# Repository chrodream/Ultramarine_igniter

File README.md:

# Ultramarine Igniter

## Specification

- Ergonomic key style
- OLED unit
- QMK Firmware is Ready
- RGB LED matrix (Optional)
- Li-Po Battery charge circuit included (Optional)

## Parts

- Ultramarine PCBs x 2
- Key switches x 70 (Cherry MX and Kailh low profile v1 are available)
- 1N4148W Diode x 70
- Pro micro x 70 (You can use BLE Pro micro when connect with Bluetooth)
- Reset switches x 2
- TRRS cable x 1 (Only wired connection)

### Optional parts

- SK6812 mini x 70

- OLED working with SSD1306 driver x 2 (128 x 32 pixels)

  #### Battery parts

  - Li-Po batteries x 2 
  - pCh MOSFET (Recommended AO3401)
  - MCP73831
  - DW01A
  - FS8205
  - 4.7uF Capacitor x 3
  - 0.1uF x 1
  - 0.1 Resistor x 1
  - 330

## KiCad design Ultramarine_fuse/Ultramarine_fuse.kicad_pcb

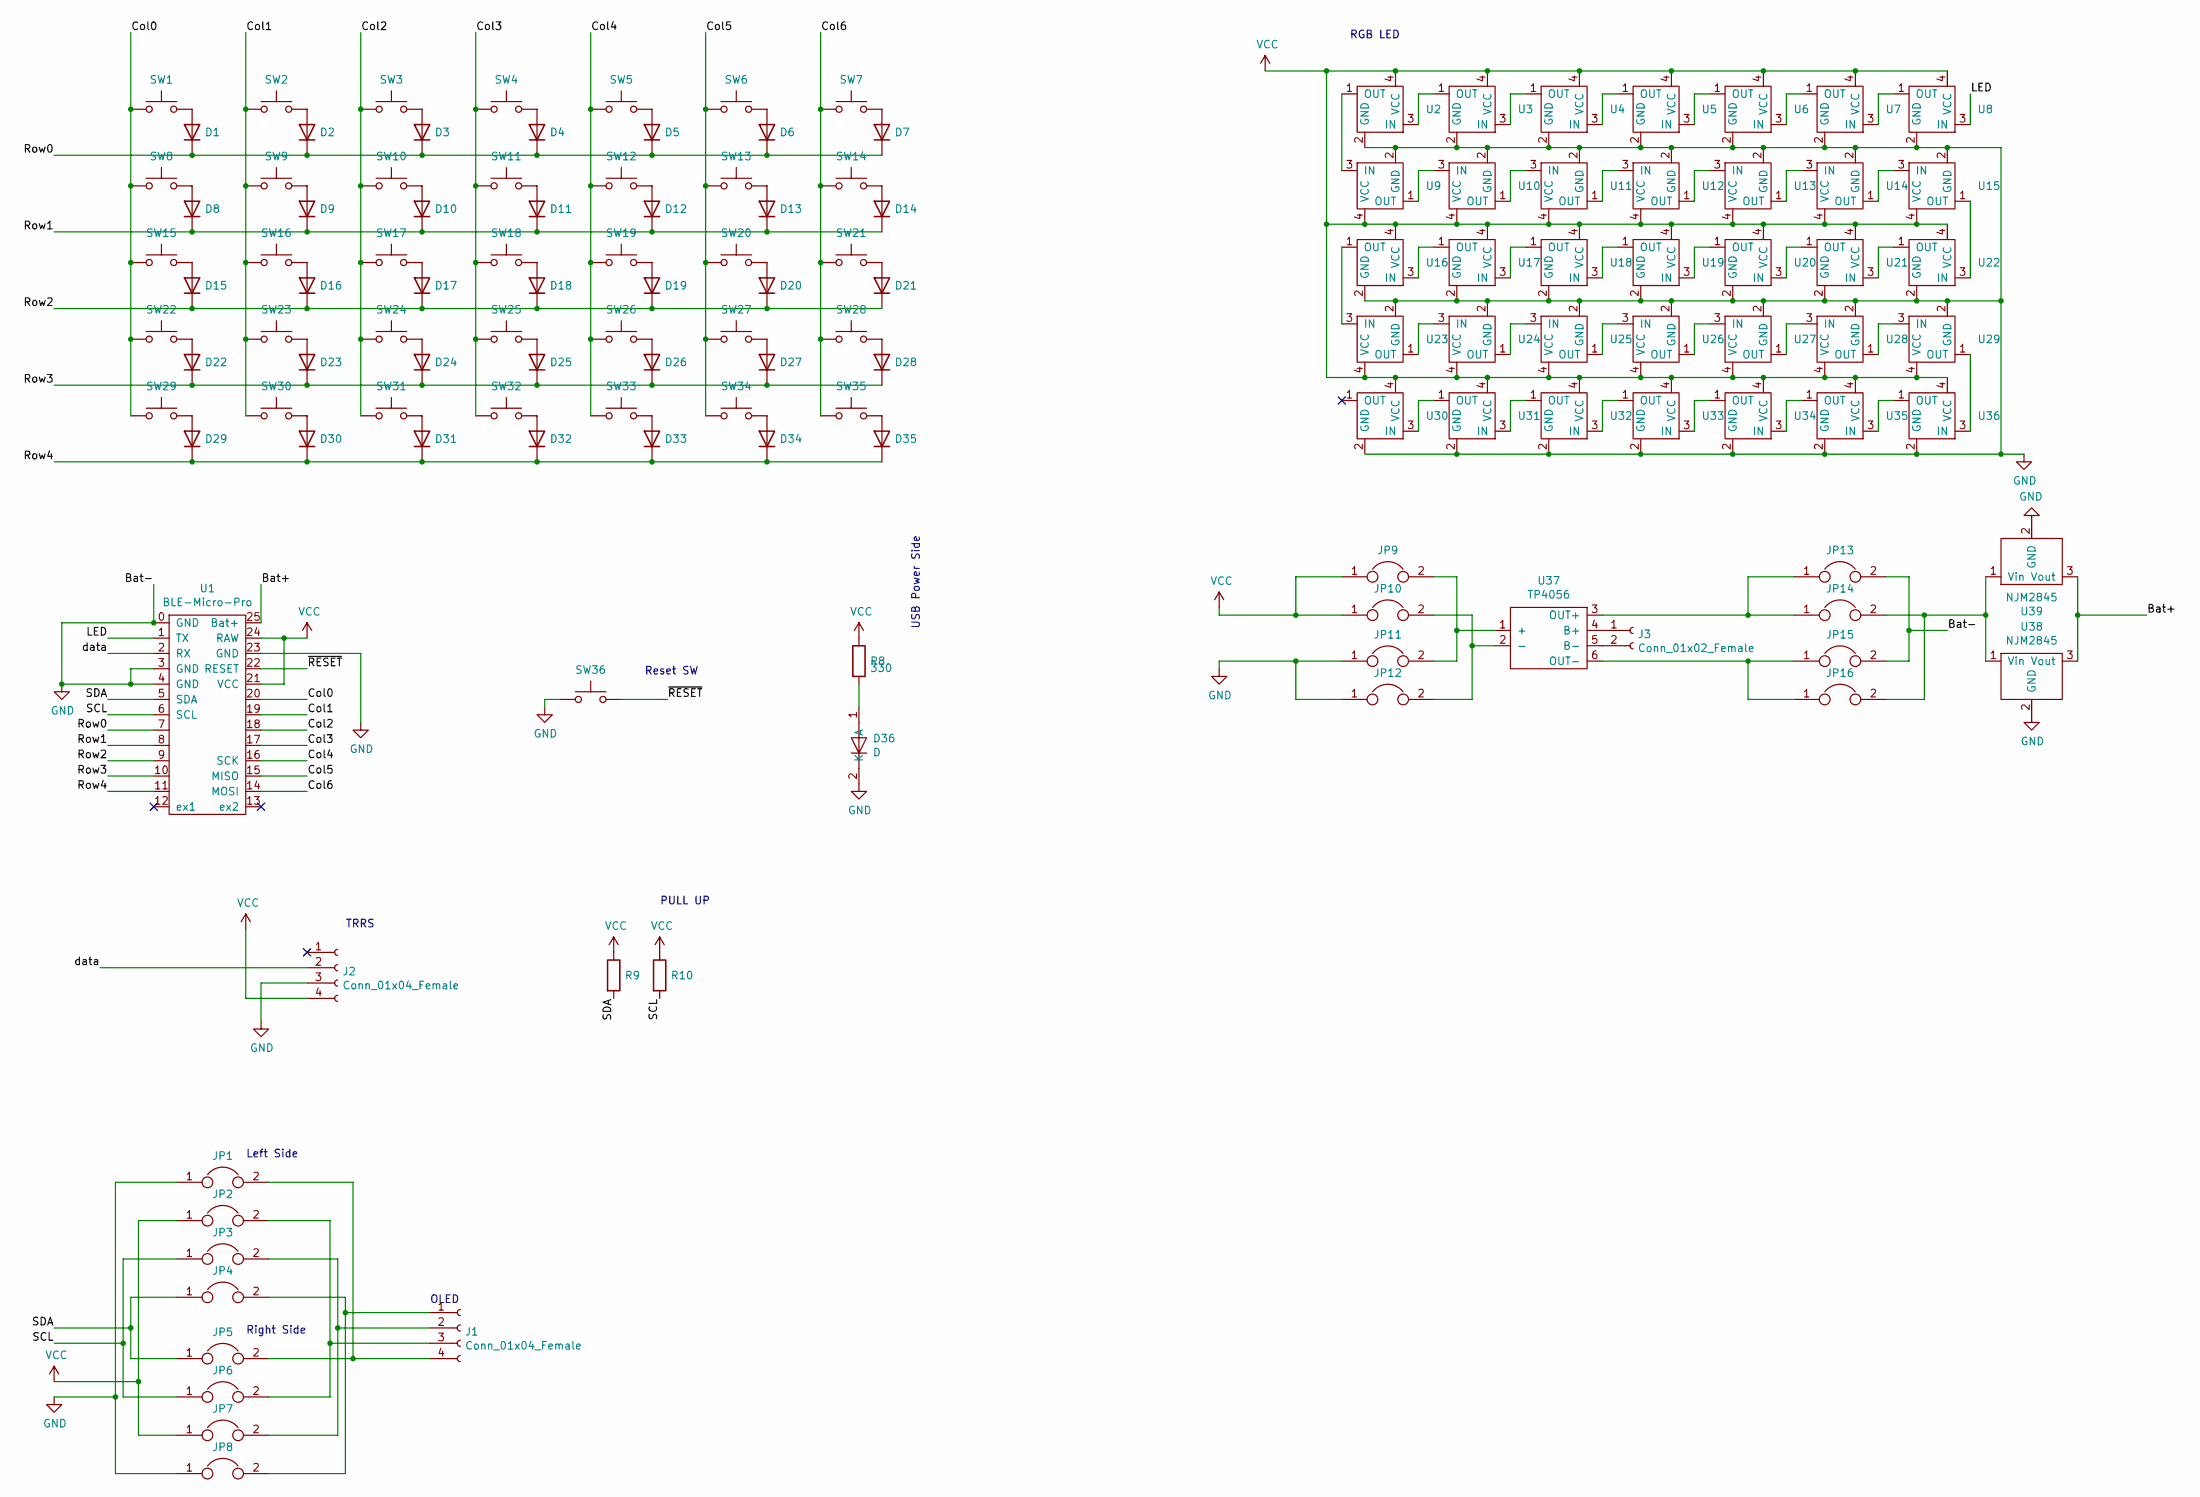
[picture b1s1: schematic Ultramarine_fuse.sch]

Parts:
D1, D2, D3, D4, D5, D6, D7, D8, D9, D10, D11, D12, D13, D14, D15, D16, D17, D18, D19, D20, D21, D22, D23, D24, D25, D26, D27, D28, D29, D30, D31, D32, D33, D34, D35: D; 1N4148
D36: D; LED1608
J1: Conn_01x04_Female; 4pin_A
J2: Conn_01x04_Female; TRRS
J3: Conn_01x02_Female; S2B-PH-K-S
JP1, JP2, JP3, JP4, JP5, JP6, JP7, JP8: Jumper; SMD_Jumper
JP9, JP10, JP11, JP12, JP13, JP14, JP15, JP16: Jumper; SolderJumper-2_P1.3mm_Open_RoundedPad1.0x1.5mm
R8: 330; 1608
R9, R10: 10K; 1608
SW1, SW2, SW3, SW4, SW5, SW6, SW7, SW8, SW9, SW10, SW11, SW12, SW13, SW14, SW15, SW16, SW17, SW18, SW19, SW20, SW21, SW22, SW23, SW24, SW25, SW26, SW27, SW28, SW29, SW30, SW31, SW32, SW33, SW34, SW35: SW_Push; MX-Kailh
SW36: SW_Push; TactSW
U1: BLE-Micro-Pro
U2, U3, U4, U5, U6, U7, U8, U9, U10, U11, U12, U13, U14, U15, U16, U17, U18, U19, U20, U21, U22, U23, U24, U25, U26, U27, U28, U29, U30, U31, U32, U33, U34, U35, U36: SK6812mini
U37: TP4056
U38, U39: NJM2845; TO-252-2

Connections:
/Bat+: U1.25 (Bat+), U38.3 (Vout), U39.3 (Vout)
/Col0: SW1.1, SW8.1, SW15.1, SW22.1, SW29.1, U1.20
/Col1: SW2.1, SW9.1, SW16.1, SW23.1, SW30.1, U1.19
/Col2: SW3.1, SW10.1, SW17.1, SW24.1, SW31.1, U1.18
/Col3: SW4.1, SW11.1, SW18.1, SW25.1, SW32.1, U1.17
/Col4: SW5.1, SW12.1, SW19.1, SW26.1, SW33.1, U1.16 (SCK)
/Col5: SW6.1, SW13.1, SW20.1, SW27.1, SW34.1, U1.15 (MISO)
/Col6: SW7.1, SW14.1, SW21.1, SW28.1, SW35.1, U1.14 (MOSI)
/LED: U1.1 (TX), U8.3 (IN)
/Row0: D1.1 (K), D2.1 (K), D3.1 (K), D4.1 (K), D5.1 (K), D6.1 (K), D7.1 (K), U1.7
/Row1: D8.1 (K), D9.1 (K), D10.1 (K), D11.1 (K), D12.1 (K), D13.1 (K), D14.1 (K), U1.8
/Row2: D15.1 (K), D16.1 (K), D17.1 (K), D18.1 (K), D19.1 (K), D20.1 (K), D21.1 (K), U1.9
/Row3: D22.1 (K), D23.1 (K), D24.1 (K), D25.1 (K), D26.1 (K), D27.1 (K), D28.1 (K), U1.10
/Row4: D29.1 (K), D30.1 (K), D31.1 (K), D32.1 (K), D33.1 (K), D34.1 (K), D35.1 (K), U1.11
/SCL: JP3.1, JP6.1, R10.2, U1.6 (SCL)
/SDA: JP4.1, JP5.1, R9.2, U1.5 (SDA)
/data: J2.2, U1.2 (RX)
/~RESET: SW36.2, U1.22 (RESET)
GND: D36.2 (K), J2.3, JP1.1, JP8.1, JP11.1, JP12.1, JP13.2, JP15.2, SW36.1, U1.0 (GND), U1.3 (GND), U1.4 (GND), U1.23 (GND), U2.2 (GND), U3.2 (GND), U4.2 (GND), U5.2 (GND), U6.2 (GND), U7.2 (GND), U8.2 (GND), U9.2 (GND), U10.2 (GND), U11.2 (GND), U12.2 (GND), U13.2 (GND), U14.2 (GND), U15.2 (GND), U16.2 (GND), U17.2 (GND), U18.2 (GND), U19.2 (GND), U20.2 (GND), U21.2 (GND), U22.2 (GND), U23.2 (GND), U24.2 (GND), U25.2 (GND), U26.2 (GND), U27.2 (GND), U28.2 (GND), U29.2 (GND), U30.2 (GND), U31.2 (GND), U32.2 (GND), U33.2 (GND), U34.2 (GND), U35.2 (GND), U36.2 (GND), U38.2 (GND), U39.2 (GND)
unnamed: D1.2 (A), SW1.2
unnamed: D2.2 (A), SW2.2
unnamed: D3.2 (A), SW3.2
unnamed: D4.2 (A), SW4.2
unnamed: D5.2 (A), SW5.2
unnamed: D6.2 (A), SW6.2
unnamed: D7.2 (A), SW7.2
unnamed: D8.2 (A), SW8.2
unnamed: D9.2 (A), SW9.2
unnamed: D10.2 (A), SW10.2
unnamed: D11.2 (A), SW11.2
unnamed: D12.2 (A), SW12.2
unnamed: D13.2 (A), SW13.2
unnamed: D14.2 (A), SW14.2
unnamed: D15.2 (A), SW15.2
unnamed: D16.2 (A), SW16.2
unnamed: D17.2 (A), SW17.2
unnamed: D18.2 (A), SW18.2
unnamed: D19.2 (A), SW19.2
unnamed: D20.2 (A), SW20.2
unnamed: D21.2 (A), SW21.2
unnamed: D22.2 (A), SW22.2
unnamed: D23.2 (A), SW23.2
unnamed: D24.2 (A), SW24.2
unnamed: D25.2 (A), SW25.2
unnamed: D26.2 (A), SW26.2
unnamed: D27.2 (A), SW27.2
unnamed: D28.2 (A), SW28.2
unnamed: D29.2 (A), SW29.2
unnamed: D30.2 (A), SW30.2
unnamed: D31.2 (A), SW31.2
unnamed: D32.2 (A), SW32.2
unnamed: D33.2 (A), SW33.2
unnamed: D34.2 (A), SW34.2
unnamed: D35.2 (A), SW35.2
unnamed: D36.1 (A), R8.2
unnamed: J1.1, JP4.2, JP8.2
unnamed: J1.2, JP3.2, JP7.2
unnamed: J1.3, JP2.2, JP6.2
unnamed: J1.4, JP1.2, JP5.2
unnamed: J3.1, U37.4 (B+)
unnamed: J3.2, U37.5 (B-)
unnamed: JP10.2, JP12.2, U37.2 (-)
unnamed: JP9.2, JP11.2, U37.1 (+)
unnamed: JP13.1, JP14.1, U37.3 (OUT+)
unnamed: JP14.2, JP16.2, U38.1 (Vin), U39.1 (Vin)
unnamed: JP15.1, JP16.1, U37.6 (OUT-)
unnamed: U2.1 (OUT), U9.3 (IN)
unnamed: U2.3 (IN), U3.1 (OUT)
unnamed: U3.3 (IN), U4.1 (OUT)
unnamed: U4.3 (IN), U5.1 (OUT)
unnamed: U5.3 (IN), U6.1 (OUT)
unnamed: U6.3 (IN), U7.1 (OUT)
unnamed: U7.3 (IN), U8.1 (OUT)
unnamed: U10.1 (OUT), U11.3 (IN)
unnamed: U9.1 (OUT), U10.3 (IN)
unnamed: U11.1 (OUT), U12.3 (IN)
unnamed: U12.1 (OUT), U13.3 (IN)
unnamed: U13.1 (OUT), U14.3 (IN)
unnamed: U14.1 (OUT), U15.3 (IN)
unnamed: U15.1 (OUT), U22.3 (IN)
unnamed: U16.1 (OUT), U23.3 (IN)
unnamed: U16.3 (IN), U17.1 (OUT)
unnamed: U17.3 (IN), U18.1 (OUT)
unnamed: U18.3 (IN), U19.1 (OUT)
unnamed: U19.3 (IN), U20.1 (OUT)
unnamed: U20.3 (IN), U21.1 (OUT)
unnamed: U21.3 (IN), U22.1 (OUT)
unnamed: U23.1 (OUT), U24.3 (IN)
unnamed: U24.1 (OUT), U25.3 (IN)
unnamed: U25.1 (OUT), U26.3 (IN)
unnamed: U26.1 (OUT), U27.3 (IN)
unnamed: U27.1 (OUT), U28.3 (IN)
unnamed: U28.1 (OUT), U29.3 (IN)
unnamed: U29.1 (OUT), U36.3 (IN)
unnamed: U30.3 (IN), U31.1 (OUT)
unnamed: U31.3 (IN), U32.1 (OUT)
unnamed: U32.3 (IN), U33.1 (OUT)
unnamed: U33.3 (IN), U34.1 (OUT)
unnamed: U34.3 (IN), U35.1 (OUT)
unnamed: U35.3 (IN), U36.1 (OUT)
VCC: J2.4, JP2.1, JP7.1, JP9.1, JP10.1, R8.1, R9.1, R10.1, U1.21 (VCC), U1.24 (RAW), U2.4 (VCC), U3.4 (VCC), U4.4 (VCC), U5.4 (VCC), U6.4 (VCC), U7.4 (VCC), U8.4 (VCC), U9.4 (VCC), U10.4 (VCC), U11.4 (VCC), U12.4 (VCC), U13.4 (VCC), U14.4 (VCC), U15.4 (VCC), U16.4 (VCC), U17.4 (VCC), U18.4 (VCC), U19.4 (VCC), U20.4 (VCC), U21.4 (VCC), U22.4 (VCC), U23.4 (VCC), U24.4 (VCC), U25.4 (VCC), U26.4 (VCC), U27.4 (VCC), U28.4 (VCC), U29.4 (VCC), U30.4 (VCC), U31.4 (VCC), U32.4 (VCC), U33.4 (VCC), U34.4 (VCC), U35.4 (VCC), U36.4 (VCC)

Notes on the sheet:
Right Side
Left Side
Reset SW
TRRS
OLED
RGB LED
PULL UP
USB Power Side

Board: 2 copper layers, 133 parts (10 on the bottom side), 101 nets, no tracks yet.

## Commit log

2021-08-27 nothing special
2021-09-19 PCB making without Charging unit is completed
2021-09-19 Update README.md
    WIP
2021-10-26 made for test printing
2021-10-26 fix circuit
2021-12-18 fixed charge circuit for TP4056
2021-12-23 add 3v3 regulator
